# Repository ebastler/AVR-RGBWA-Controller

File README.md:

## AVR RGBWA Controller
### Overview
This project was born as an ambient light for a living room. I wanted five controllable LED channels and compatibility with 12 V or 24 V LED stripes and an easy to use interface with a single rotary encoder (and it's push button). As a controller I chose an "Arduino pro Micro" from China, because I wanted to be able to add USB support later on and the arduino features an ATmega32U4 with all necessary external components. It was, however, programmed entirely in C without any Arduino-headers or library.

### Schematic and Layout
I tried to only use cheap and easily available standard components, all of which should be available at my usual component shop, Reichelt.de.
While the Layout was made using almost entirely SMD components, all footprints are large enough to be easily soldered by hand without SMD soldering experience or expensive equipment.
The double sided layout itself needed a fair amount of VIAs, but it should be possible to manufacture it at home with a bit of experience in making PCBs.

Eagle files, Gerber Files and pdf layouts, as well as pngs of both layers and the schematic can be found in the PCB folder.

The Arduino can be directly soldered onto the PCB using pin headers and programmed with a 6pin ISP port

### Code
The code is written in plain C, without relying on any non-standard libraries. I have written and compiled it with the most recent version of Atmel Studio, which handles most standard library includes and compiler options by itself, so I will only upload the plain .c file without a makefile apart from the compiled .hex.

I am using the [rotary encoder example of Peter Dannegger](https://www.mikrocontroller.net/articles/Drehgeber "microcontroller.net"). I slightly adapted it to my needs, but left it mostly unchanged.

The push-button as well as the rotary encoder are software-debounced and checked using interrupts.
Some values can be set in the variable definitions at the beginning of the file (initial WA value, initial RGB value, initial brightness, initial colow-sweep speed).

The LEDs are controlled using a soft PWM loop.

### Use
The controller must be fed with a voltage between 8 V and 30V DC, I would recommend using 12 V or 24 V and Common Anode LED stripes with the same operating voltage. Stripes are connected to the terminals next to the power jack. The closest terminal is the positive voltage, the others are the open drain outputs, which are supposed to be connected with the negative wire(s) of the stripes in the following order: R-G-B-W-A-X (X being an unused channel at constant 50% duty cycle in my code, brightness is applied to it as well).
It is controlled with a single rotary encoder and it's push button. A short click on the encoder cycles between the three available lighting modes.

Modes:
1. White: Rotating the encoder changes the balance between warm white and cold white (startup value being both at full power). It is possible to scroll "endlessly" - the colors will loop and no hard transition is visible.
2. RGB Manual: Rotating the encoder cycles through the RGB spectrum with a simple algorithm that never uses more than 2 colors at the same time. It is possible to scroll "endlessly" - the colors will loop and no hard transition is visible.
3. RGB Automatic: The controller automatically cycles through the RGB spectrum and behaves as if the user was constantly rotating the encoder. Operating the encoder in this mode changes the speed with which the colors fade (clockwise -> faster).
A short click in the third mode leads back to the first.

All modes can be interrupted at any point by a long click (~.5s), which will lead to the brightness control function. Here, the encoder controls the brightness which is globally applied to all channels and modes. A short click exits the brightness control and leads back to the mode that was active before.

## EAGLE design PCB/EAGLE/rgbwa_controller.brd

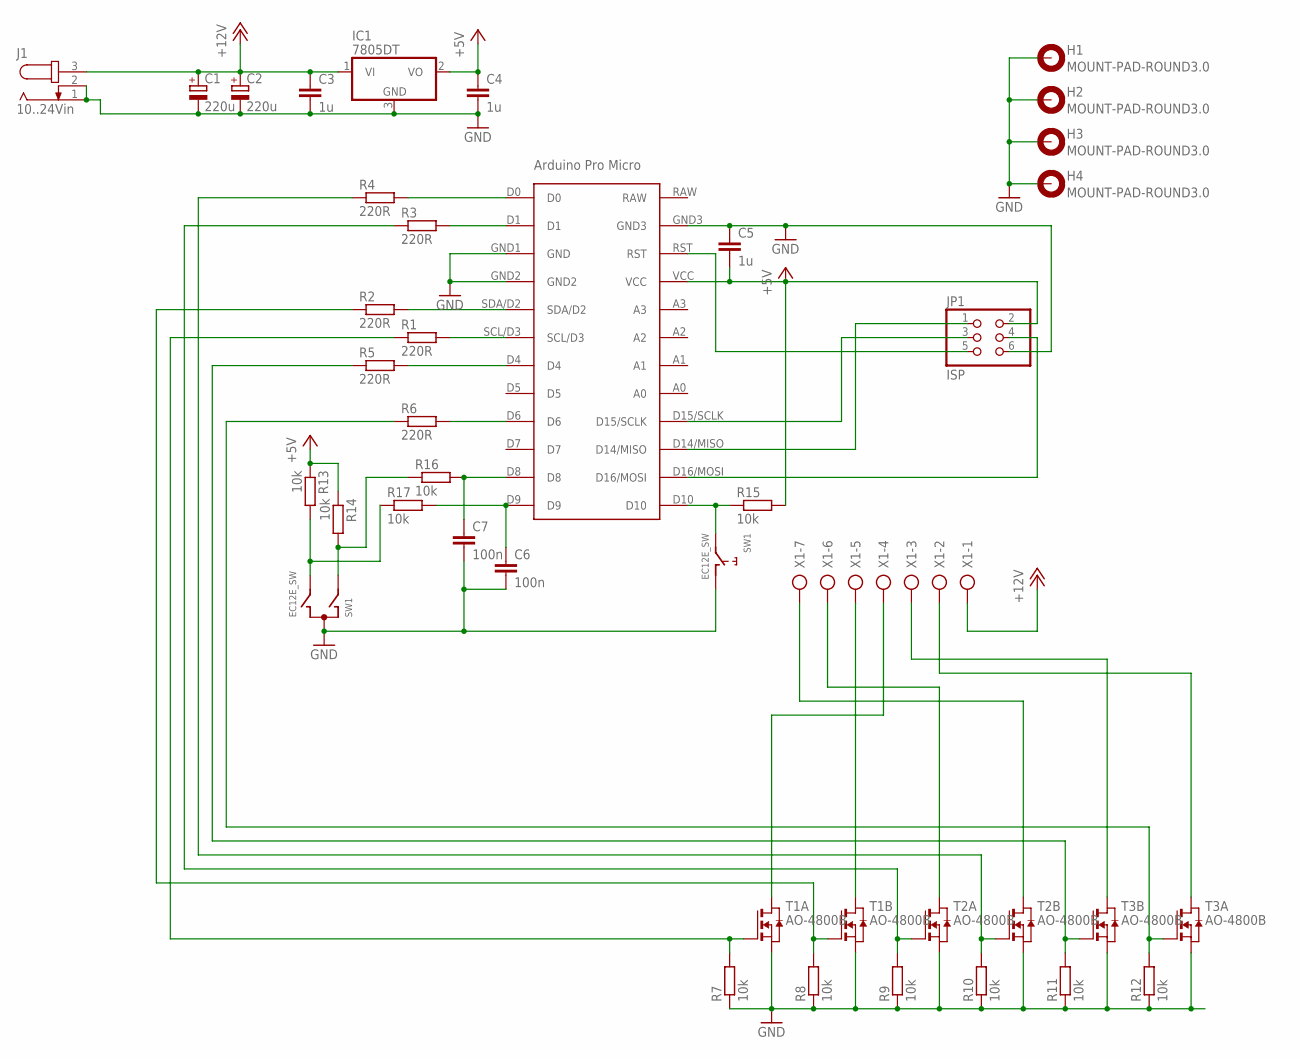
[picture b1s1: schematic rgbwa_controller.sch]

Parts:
C1, C2: 220u; 150CLZ-1010
C3, C4, C5: 1u; C1206
C6, C7: 100n; C0805
H1, H2, H3, H4: MOUNT-PAD-ROUND3.0; 3,0-PAD
IC1: 7805DT; TO252
J1: 10..24Vin; SPC4078
JP1: ISP; 2X03
R1, R2, R3, R4, R5, R6: 220R; M0805
R7, R8, R9, R10, R11, R12, R13, R14, R15, R16, R17: 10k; M0805
SW1: EC12E_SW; ALPS_EC12E_SW
T1, T2, T3: AO-4800B; SM8
U$1: PROMICRO
X1: AK300/7

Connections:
+5V: C4.1, C5.2, IC1.2 (VO), JP1.2, R13.1, R14.1, R15.2, U$1.VCC
+12V: C1.+, C2.+, C3.1, IC1.1 (VI), J1.3, X1.1
GND: C1.-, C2.-, C3.2, C4.2, C5.1, C6.2, C7.2, H1.B3,0, H2.B3,0, H3.B3,0, H4.B3,0, IC1.3 (GND), J1.1, J1.2, JP1.6, R7.1, R8.1, R9.1, R10.1, R11.1, R12.1, SW1.C, SW1.D (1), T1.1 (S), T1.3 (S), T2.1 (S), T2.3 (S), T3.1 (S), T3.3 (S), U$1.GND1 (GND), U$1.GND2, U$1.GND3
unnamed: R4.2, U$1.D0
unnamed: R3.2, U$1.D1
unnamed: R2.2, U$1.SDA/D2
unnamed: R1.2, U$1.SCL/D3
unnamed: R5.2, U$1.D4
unnamed: R6.2, U$1.D6
unnamed: R1.1, R7.2, T1.2 (G)
unnamed: R2.1, R8.2, T1.4 (G)
unnamed: R3.1, R9.2, T2.2 (G)
unnamed: R4.1, R10.2, T2.4 (G)
unnamed: R5.1, R11.2, T3.4 (G)
unnamed: R6.1, R12.2, T3.2 (G)
unnamed: R13.2, R17.1, SW1.B
unnamed: JP1.1, U$1.D14/MISO
unnamed: T3.7 (D), T3.8 (D), X1.2
unnamed: T1.5 (D), T1.6 (D), X1.5
unnamed: T1.7 (D), T1.8 (D), X1.4
unnamed: R14.2, R16.1, SW1.A
unnamed: JP1.3, U$1.D15/SCLK
unnamed: C6.1, R17.2, U$1.D9
unnamed: R15.1, SW1.E (2), U$1.D10
unnamed: C7.1, R16.2, U$1.D8
unnamed: JP1.5, U$1.RST
unnamed: T3.5 (D), T3.6 (D), X1.3
unnamed: T2.5 (D), T2.6 (D), X1.7
unnamed: T2.7 (D), T2.8 (D), X1.6
unnamed: JP1.4, U$1.D16/MOSI

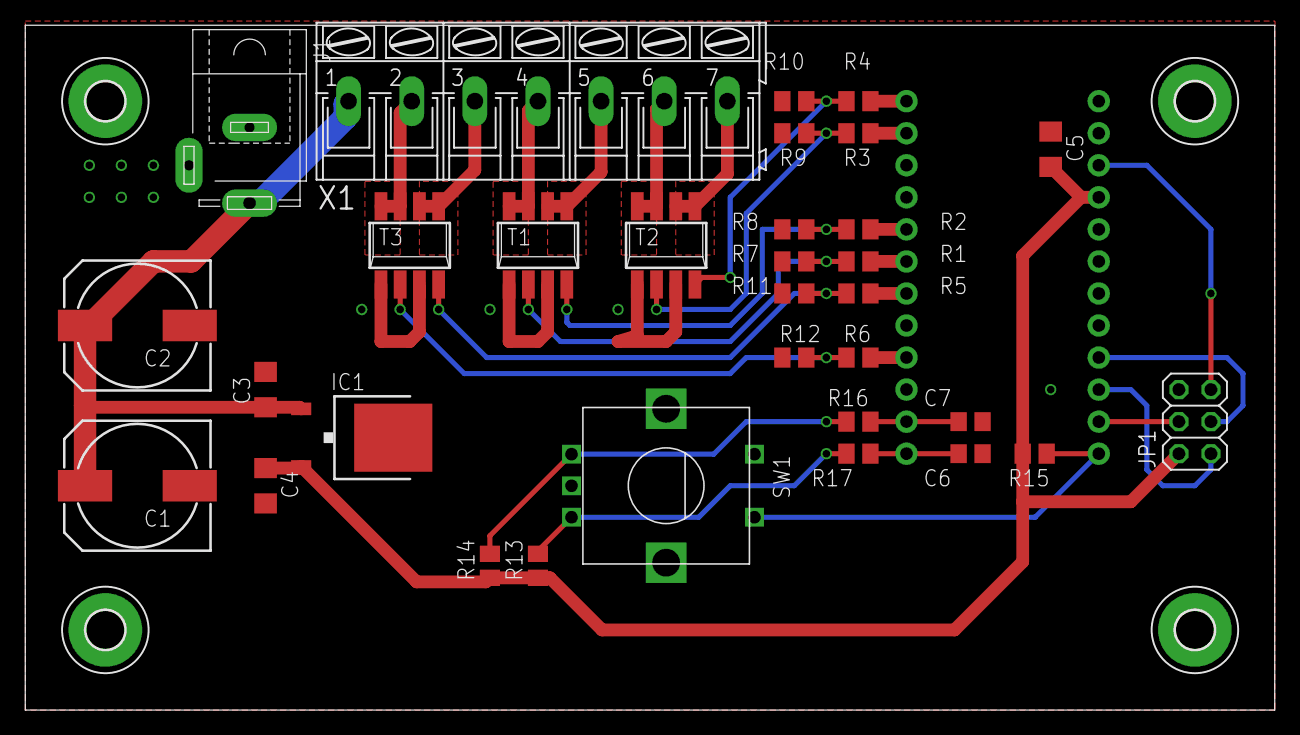
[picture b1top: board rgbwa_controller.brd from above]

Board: 2 copper layers, 99.0 x 54.3 mm, 37 parts (0 on the bottom side), 30 nets.

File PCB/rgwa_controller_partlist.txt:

Partlist

Exported from rgbwa.sch at 23/05/2018 21:52:27

EAGLE Version 7.1.0 Copyright (c) 1988-2014 CadSoft

Assembly variant: 

Part     Value              Device             Package       Library           Sheet

C1       220u               CPOL-EU150CLZ-1010 150CLZ-1010   rcl               1
C2       220u               CPOL-EU150CLZ-1010 150CLZ-1010   rcl               1
C3       1u                 C-EUC1206          C1206         rcl               1
C4       1u                 C-EUC1206          C1206         rcl               1
C5       1u                 C-EUC1206          C1206         rcl               1
C6       100n               C-EUC0805          C0805         rcl               1
C7       100n               C-EUC0805          C0805         rcl               1
IC1      7805DT             7805DT             TO252         linear            1
J1       10..24Vin          JACK-PLUG1         SPC4078       con-jack          1
JP1      ISP                PINHD-2X3          2X03          pinhead           1
R1       220R               R-EU_M0805         M0805         rcl               1
R2       220R               R-EU_M0805         M0805         rcl               1
R3       220R               R-EU_M0805         M0805         rcl               1
R4       220R               R-EU_M0805         M0805         rcl               1
R5       220R               R-EU_M0805         M0805         rcl               1
R6       220R               R-EU_M0805         M0805         rcl               1
R7       10k                R-EU_M0805         M0805         rcl               1
R8       10k                R-EU_M0805         M0805         rcl               1
R9       10k                R-EU_M0805         M0805         rcl               1
R10      10k                R-EU_M0805         M0805         rcl               1
R11      10k                R-EU_M0805         M0805         rcl               1
R12      10k                R-EU_M0805         M0805         rcl               1
R13      10k                R-EU_M0805         M0805         rcl               1
R14      10k                R-EU_M0805         M0805         rcl               1
R15      10k                R-EU_M0805         M0805         rcl               1
R16      10k                R-EU_M0805         M0805         rcl               1
R17      10k                R-EU_M0805         M0805         rcl               1
SW1      EC12E_SW           EC12E_SW           ALPS_EC12E_SW switch-alps       1
T1       AO-4800B           NMOS2SM8           SM8           zetex             1
T2       AO-4800B           NMOS2SM8           SM8           zetex             1
T3       AO-4800B           NMOS2SM8           SM8           zetex             1
U$1      PROMICRO           PROMICRO           PROMICRO      arduino pro micro 1
X1                          AK300/7            AK300/7       con-ptr500        1

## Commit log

2018-05-23 fixed typos in readme
2018-05-23 fixed some git noob mistakes
